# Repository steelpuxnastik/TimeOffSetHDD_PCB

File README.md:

# TimeOffSetHDD_PCB
Old notebook Acer 5560G has problem in using second HDD, which connects to the slot of the DVD drive. PC will not start, if HDD connected, but PC and second HDD works fine if HDD will be conected after Power-On Self-Test (POST). More info here: https://habr.com/ru/post/215839/ (here is described an example of creating a relay-based power delay circuit).

But the above scheme has several disadvantages, some of which inability to reboot (notebook will not pass POST) and some bulkiness and design complexity. In addition, the author of the above article himself says that he offers all this as an example, confirming that the method itself is working and that simpler implementations are possible.

Field notes: as I can see, the problem lies in the fact that the BIOS, in principle, is not provided for booting with two hard drives, since there is only one HDD0 and when notebook detects second HDD - it cannot determine what exactly HDD is primary and what HDD is second because BIOS knows only 1 HDD it can operate, so after that it has problem with POST, because it do not knows how to solve that problem.

That is why I tried to make much smaller and more controlled scheme on Attiny13A and transistor IRF7204, which controls power supply through the transistor (transistor opens in 10 sec after applying power to the MCU and turning on the second HDD). 
Parts used:
1. ATTINY13A-SU
2. IRF7204 Transistor
3. VT 10uF 25V 4 * 5.4 105C SMD Capacitor x1 
4. 5.6K 0603 5% SMD Resistor x2
5. XH-03A connector (to connect input 5V, output 5V and ground from HDD caddy)
6. Pin header 2x3pin 2.54mm for SPI MCU programming (the arrangement of contacts is duplicated from Arduino ICSP)

Result:

Program can be flashed through Arduino IDE as Arduino SPI programmer.
You need to download this archive ( https://github.com/orlv/at13/archive/master.zip ) and unzip it into your default folder with scatches, usually it's "\Documents\Arduino\hardware\" (in result it must be something like this "C:\Users\Администратор\Documents\Arduino\hardware\attiny13\avr\cores\core13").
Then flash your Arduino with scatch from Arduino IDE Samples - ArduinoISP
Afrer that connect ATtiny13 to Arduino similar to the ICSP block on Arduino, but last RESET pin on device connect to pin 10 on Arduino.

Choose the board Attiny13 in menu Tools and I would recommend to choose "Frequency: 128kHz", because we do not need more - MCU literally will do nothing more, but it will help tremendously reduce its consumption of power.

Then choose "Arduino as ISP" in "Tools - Programmer" (or "Arduino as ISP (ATmega32U4)" if you have Leonardo like me, simply on "Arduino as ISP" my Leonardo is not flashing MCU) press "Burn bootloader". This will flash to MCU settings that we selected earlier.
After that you can flash the programm.

Device works well only if notebook starts from total turn off (best variants is to turn off by button after set "restart" in Windows, because notebook will not start after that, so you need to turn it off by button and then turn it on and then notebook will start well with second HDD). Delay time was shorted to 2 sec - it's minimum delay time needed to start.

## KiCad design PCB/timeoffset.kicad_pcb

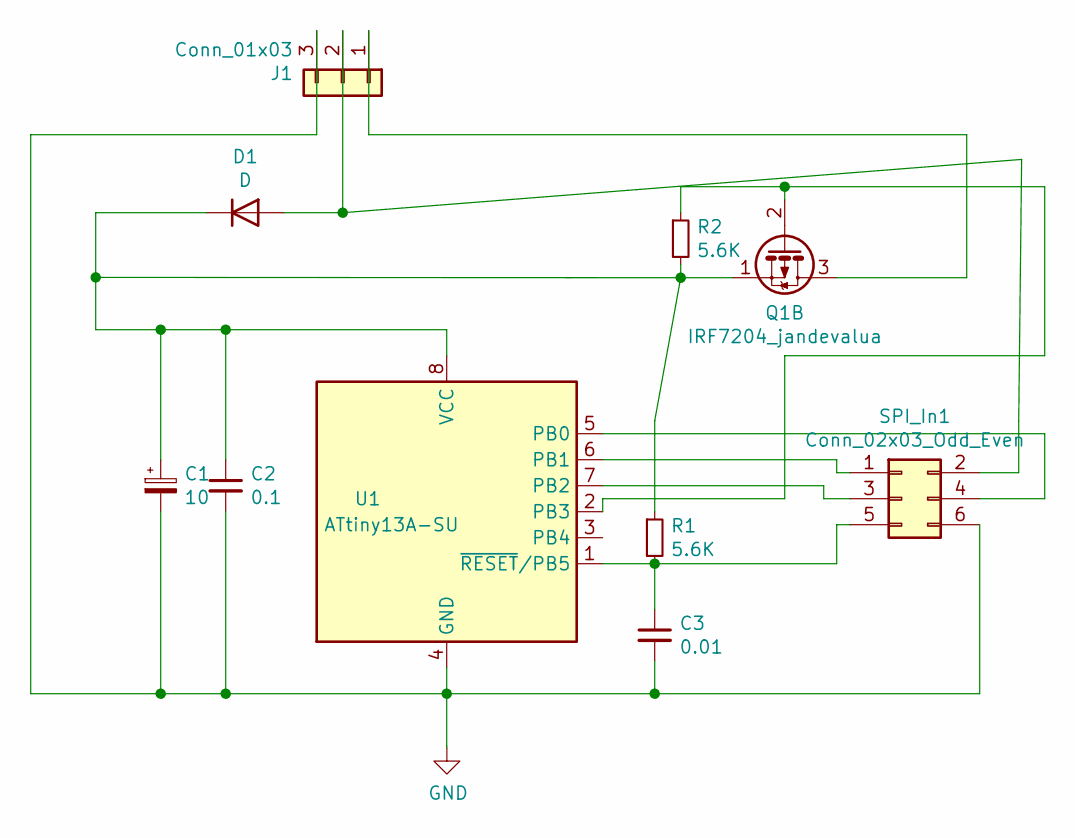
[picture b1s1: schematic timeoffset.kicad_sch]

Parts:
C1: 10; C_Elec_4x5.4
C2: 0.1; C_0603_1608Metric
C3: 0.01; C_0603_1608Metric
D1: D; D_SMA
J1: Conn_01x03; JST_PH_S3B-PH-K_1x03_P2.00mm_Horizontal
Q1: IRF7204_jandevalua; SOIC-8_3.9x4.9mm_P1.27mm
R1, R2: 5.6K; R_0603_1608Metric
SPI_In1: Conn_02x03_Odd_Even; PinHeader_2x03_P2.54mm_Horizontal
U1: ATtiny13A-SU; SOIJ-8_5.3x5.3mm_P1.27mm

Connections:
GND: C1.2, C2.2, C3.2, J1.3, SPI_In1.6, U1.4 (GND)
unnamed: C1.1, C2.1, D1.1 (K), Q1.1 (S2), R1.1, R2.2, U1.8 (VCC)
unnamed: C3.1, R1.2, SPI_In1.5, U1.1 (~RESET/PB5)
unnamed: D1.2 (A), J1.2, SPI_In1.2
unnamed: J1.1, Q1.3 (D2)
unnamed: Q1.2 (G2), R2.1, U1.2 (PB3)
unnamed: SPI_In1.1, U1.6 (PB1)
unnamed: SPI_In1.3, U1.7 (PB2)
unnamed: SPI_In1.4, U1.5 (PB0)

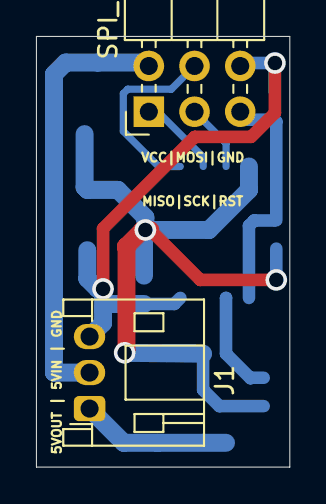
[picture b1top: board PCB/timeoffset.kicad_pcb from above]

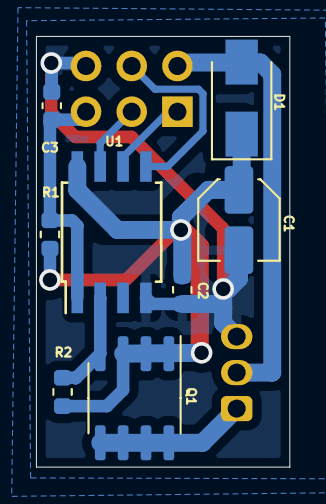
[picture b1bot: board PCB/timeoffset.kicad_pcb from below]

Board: 2 copper layers, 14.1 x 23.9 mm, 10 parts (8 on the bottom side), 9 nets.

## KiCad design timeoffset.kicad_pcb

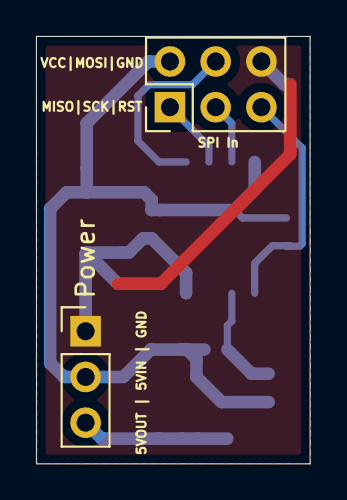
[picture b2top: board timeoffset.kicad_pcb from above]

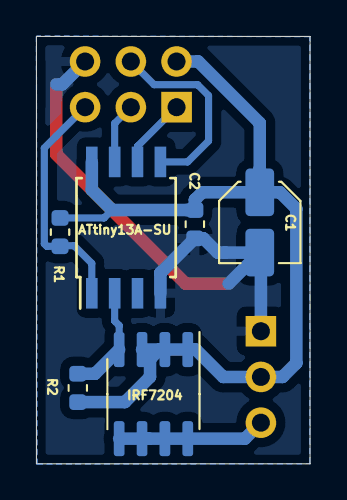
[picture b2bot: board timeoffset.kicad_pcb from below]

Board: 2 copper layers, 15.2 x 23.7 mm, 8 parts (6 on the bottom side), 8 nets.

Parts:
ATtiny13A-SU: ATtiny13A-SU; SOIJ-8_5.3x5.3mm_P1.27mm
C1: 10; C_Elec_4x5.4
C2: 0.1; C_0603_1608Metric
IRF7204: IRF7204_jandevalua; SOIC-8_3.9x4.9mm_P1.27mm
Power: Conn_01x03; PinHeader_1x03_P2.54mm_Vertical
R1, R2: 5.6K; R_0603_1608Metric
SPI In: Conn_02x03_Odd_Even; PinHeader_2x03_P2.54mm_Vertical

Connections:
unnamed: ATtiny13A-SU.8, C1.1, C2.1, IRF7204.1, Power.2, R1.1, R2.2, SPI In.2
unnamed: ATtiny13A-SU.4, C1.2, C2.2, Power.1, SPI In.6
unnamed: IRF7204.3, Power.3
unnamed: ATtiny13A-SU.2, IRF7204.2, R2.1
unnamed: ATtiny13A-SU.1, R1.2, SPI In.5
unnamed: ATtiny13A-SU.6, SPI In.1
unnamed: ATtiny13A-SU.7, SPI In.3
unnamed: ATtiny13A-SU.5, SPI In.4

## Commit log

2019-12-11 Little fixes
2019-12-29 The device is assembled, the program is written - it basically works
    The device is assembled, the program is written - it basically works. Need final tests on the hard drive itself
2019-12-29 images of ready PCB
    images of ready PCB
2019-12-30 images
2020-01-20 Changed settings and mounted images
2020-01-26 ideas about adding reboot support
2021-09-06 Update, will finally try it very soon, I hope
2021-09-06 Smaller form
2021-09-06 board optimization
2021-09-09 horizontal connectors added
2021-09-10 Reset fix
